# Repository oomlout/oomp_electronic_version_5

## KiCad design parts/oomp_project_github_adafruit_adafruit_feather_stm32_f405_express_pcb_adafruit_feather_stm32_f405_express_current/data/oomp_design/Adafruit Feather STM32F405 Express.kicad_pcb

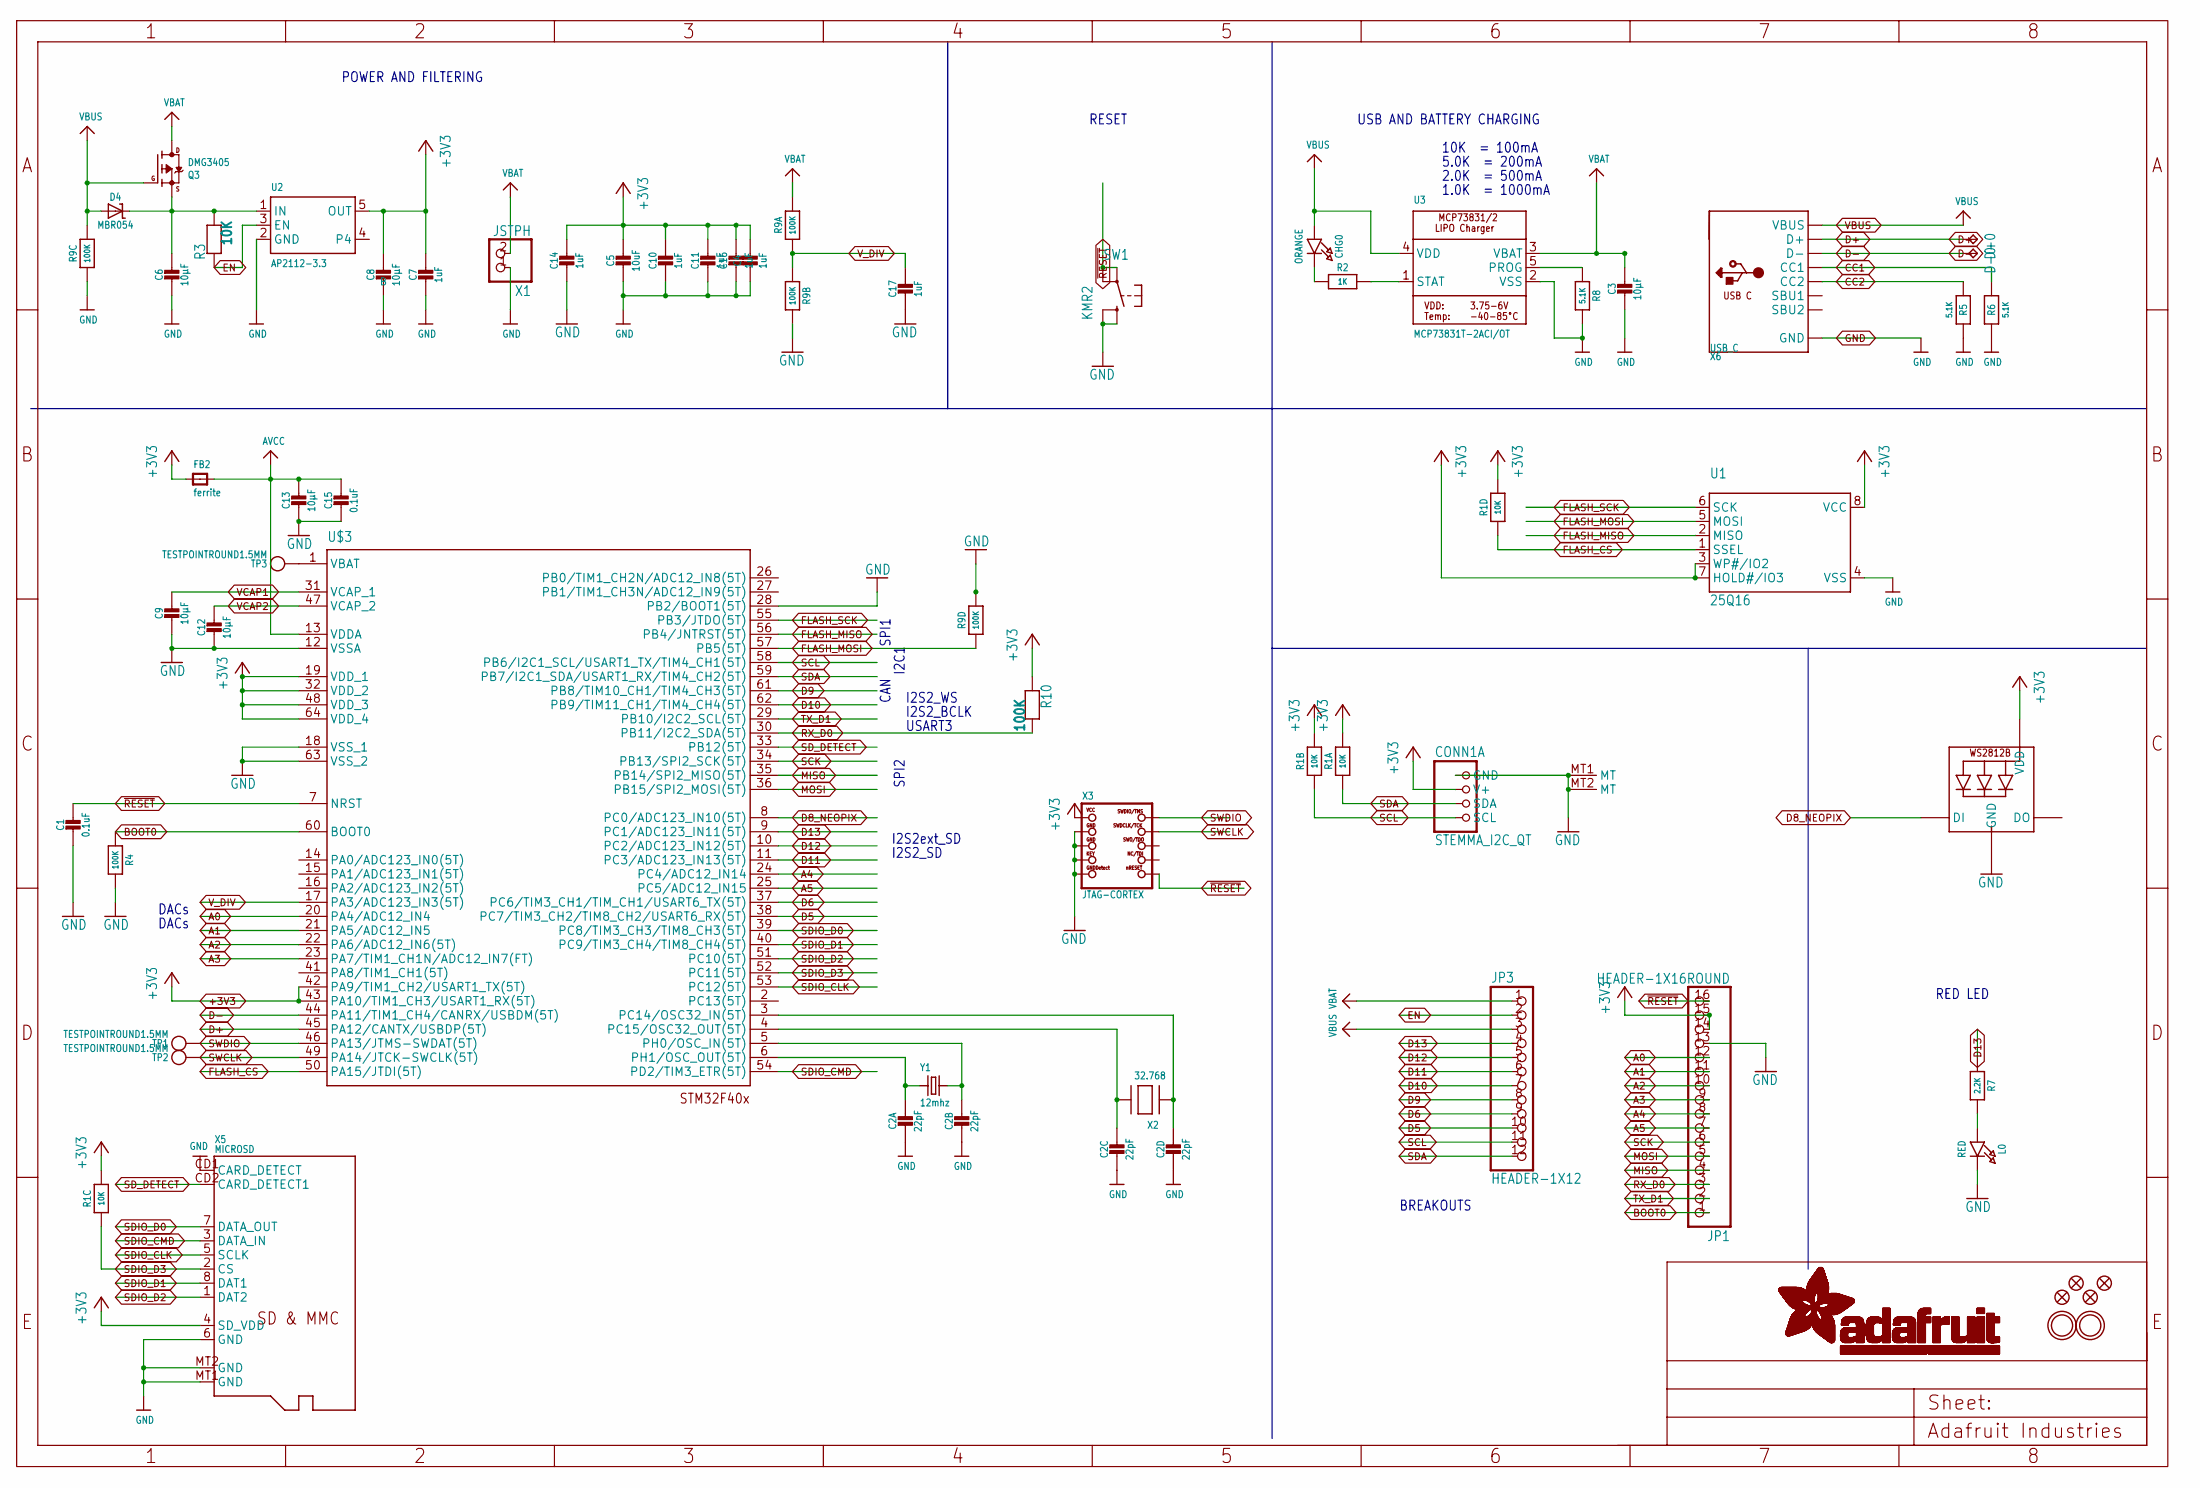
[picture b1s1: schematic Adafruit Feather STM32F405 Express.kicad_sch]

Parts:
C1, C15: 0.1uF; 0603-NO
C2: 22pF; RESPACK_4X0603
C3, C6, C8, C9, C12, C13: 10µF; 0805-NO
C4, C7, C10, C11, C14, C16, C17: 1uF; 0603-NO
C5: 10uF; 0805-NO
CHG0: ORANGE; CHIPLED_0805_NOOUTLINE
CONN1: STEMMA_I2C_QT; JST_SH4
D4: MBR054; SOD-123
D+0: TPB1,27; B1,27
D-0: TPB1,27; B1,27
FB2: ferrite; 0805-NO
JP1: HEADER-1X16ROUND; 1X16_ROUND
JP3: HEADER-1X12; 1X12_ROUND
L0: RED; CHIPLED_0805_NOOUTLINE
LED1: WS2812B3535; LED3535
Q3: DMG3405; SOT23-R
R1: 10K; RESPACK_4X0603_NO
R2: 1K; 0603-NO
R3: 10K; 0603-NO
R4, R10: 100K; 0603-NO
R5, R6, R8: 5.1K; 0603-NO
R7: 2.2K; 0603-NO
R9: 100K; RESPACK_4X0603_NO
SW1: KMR2; BTN_KMR2_4.6X2.8
TP1, TP2, TP3: TESTPOINTROUND1.5MM; TESTPOINT_ROUND_1.5MM
U1: 25Q16; SOIC8_150MIL
U2: AP2112-3.3; SOT23-5
U3: MCP73831T-2ACI/OT; SOT23-5
U$3: STM32F405R; TQFP64
U$5, U$34, U$35, U$37: FIDUCIAL_1MM
U$31, U$32: MOUNTINGHOLE2.5; MOUNTINGHOLE_2.5_PLATED
X1: JSTPH; JSTPH2
X2: 32.768; XTAL3215
X3: JTAG-CORTEX; 2X05_1.27MM_SMT
X5: MICROSD
X6: USB_C; USB_C_CUSB31-CFM2AX-01-X
Y1: 12mhz; CRYSTAL_2.5X2

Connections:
+3V3: C4.1, C5.1, C7.1, C8.1, C10.1, C11.1, C14.1, C16.1, CONN1.2 (V+), FB2.1, JP1.14, JP1.15, LED1.2 (VDD), R1.5 (2), R1.6 (2), R1.7 (2), R1.8 (2), R10.1, U1.3 (WP#/IO2), U1.7 (HOLD#/IO3), U1.8 (VCC), U2.5 (OUT), U$3.19 (VDD_1), U$3.32 (VDD_2), U$3.42 (PA9/TIM1_CH2/USART1_TX(5T)), U$3.43 (PA10/TIM1_CH3/USART1_RX(5T)), U$3.48 (VDD_3), U$3.64 (VDD_4), X3.1 (VCC), X5.4 (SD_VDD)
A0: JP1.12, U$3.20 (PA4/ADC12_IN4)
A1: JP1.11, U$3.21 (PA5/ADC12_IN5)
A2: JP1.10, U$3.22 (PA6/ADC12_IN6(5T))
A3: JP1.9, U$3.23 (PA7/TIM1_CH1N/ADC12_IN7(FT))
A4: JP1.8, U$3.24 (PC4/ADC12_IN14)
A5: JP1.7, U$3.25 (PC5/ADC12_IN15)
AVCC: C13.1, C15.1, FB2.2, U$3.13 (VDDA)
BATTERY: TP3.P$1, U$3.1 (VBAT)
BOOT0: JP1.1, R4.1, U$3.60 (BOOT0)
CC1: R6.2, X6.A5 (CC1)
CC2: R5.2, X6.B5 (CC2)
D5: JP3.10, U$3.38 (PC7/TIM3_CH2/TIM8_CH2/USART6_RX(5T))
D6: JP3.9, U$3.37 (PC6/TIM3_CH1/TIM_CH1/USART6_TX(5T))
D8_NEOPIX: LED1.1 (DI), U$3.8 (PC0/ADC123_IN10(5T))
D9: JP3.8, U$3.61 (PB8/TIM10_CH1/TIM4_CH3(5T))
D10: JP3.7, U$3.62 (PB9/TIM11_CH1/TIM4_CH4(5T))
D11: JP3.6, U$3.11 (PC3/ADC123_IN13(5T))
D12: JP3.5, U$3.10 (PC2/ADC123_IN12(5T))
D13: JP3.4, R7.1, U$3.9 (PC1/ADC123_IN11(5T))
D+: D+0.TP, U$3.45 (PA12/CANTX/USBDP(5T)), X6.A6 (D+), X6.B6 (D+)
D-: D-0.TP, U$3.44 (PA11/TIM1_CH4/CANRX/USBDM(5T)), X6.A7 (D-), X6.B7 (D-)
EN: JP3.2, R3.1, U2.3 (EN)
FLASH_CS: R1.4 (1), U1.1 (SSEL), U$3.50 (PA15/JTDI(5T))
FLASH_MISO: U1.2 (MISO), U$3.56 (PB4/JNTRST(5T))
FLASH_MOSI: R9.4 (1), U1.5 (MOSI), U$3.57 (PB5(5T))
FLASH_SCK: U1.6 (SCK), U$3.55 (PB3/JTDO(5T))
GND: C1.2, C2.5 (2), C2.6 (2), C2.7 (2), C2.8 (2), C3.2, C4.2, C5.2, C6.2, C7.2, C8.2, C9.2, C10.2, C11.2, C12.2, C13.2, C14.2, C15.2, C16.2, C17.2, CONN1.1 (GND), CONN1.MT1 (MT), CONN1.MT2 (MT), JP1.13, L0.C, LED1.4 (GND), R4.2, R5.1, R6.1, R8.2, R9.3 (1), R9.5 (2), R9.7 (2), SW1.B (S), SW1.B' (S1), U1.4 (VSS), U2.2 (GND), U3.2 (VSS), U$3.12 (VSSA), U$3.18 (VSS_1), U$3.28 (PB2/BOOT1(5T)), U$3.63 (VSS_2), X1.1, X3.3 (GND), X3.5 (GND), X3.7 (KEY), X3.9 (GNDDETECT), X5.6 (GND), X5.CD1 (CARD_DETECT), X5.MT1 (GND), X5.MT2 (GND), X6.A1B12 (GND), X6.B1A12 (GND)
MISO: JP1.4, U$3.35 (PB14/SPI2_MISO(5T))
MOSI: JP1.5, U$3.36 (PB15/SPI2_MOSI(5T))
unnamed: CHG0.C, R2.1
unnamed: L0.A, R7.2
unnamed: R2.2, U3.1 (STAT)
unnamed: R8.1, U3.5 (PROG)
unnamed: C2.4 (1), U$3.3 (PC14/OSC32_IN(5T)), X2.P$1
unnamed: C2.2 (1), U$3.5 (PH0/OSC_IN(5T)), Y1.3 (2)
unnamed: C2.3 (1), U$3.4 (PC15/OSC32_OUT(5T)), X2.P$2
unnamed: C2.1, U$3.6 (PH1/OSC_OUT(5T)), Y1.1
RX_D0: JP1.3, R10.2, U$3.30 (PB11/I2C2_SDA(5T))
SCK: JP1.6, U$3.34 (PB13/SPI2_SCK(5T))
SCL: CONN1.4 (SCL), JP3.11, R1.2 (1), U$3.58 (PB6/I2C1_SCL/USART1_TX/TIM4_CH1(5T))
SDA: CONN1.3 (SDA), JP3.12, R1.1, U$3.59 (PB7/I2C1_SDA/USART1_RX/TIM4_CH2(5T))
SDIO_CLK: U$3.53 (PC12(5T)), X5.5 (SCLK)
SDIO_CMD: U$3.54 (PD2/TIM3_ETR(5T)), X5.3 (DATA_IN)
SDIO_D0: U$3.39 (PC8/TIM3_CH3/TIM8_CH3(5T)), X5.7 (DATA_OUT)
SDIO_D1: U$3.40 (PC9/TIM3_CH4/TIM8_CH4(5T)), X5.8 (DAT1)
SDIO_D2: U$3.51 (PC10(5T)), X5.1 (DAT2)
SDIO_D3: R1.3 (1), U$3.52 (PC11(5T)), X5.2 (CS)
SD_DETECT: U$3.33 (PB12(5T)), X5.CD2 (CARD_DETECT1)
SWCLK: TP2.P$1, U$3.49 (PA14/JTCK-SWCLK(5T)), X3.4 (SWDCLK)
SWDIO: TP1.P$1, U$3.46 (PA13/JTMS-SWDAT(5T)), X3.2 (SWDIO)
TX_D1: JP1.2, U$3.29 (PB10/I2C2_SCL(5T))
VBAT: C3.1, JP3.1, Q3.3 (D), R9.8 (2), U3.3 (VBAT), X1.2
VBUS: CHG0.A, D4.A, JP3.3, Q3.1 (G), R9.6 (2), U3.4 (VDD), X6.A4B9 (VBUS), X6.B4A9 (VBUS)
VCAP1: C9.1, U$3.31 (VCAP_1)
VCAP2: C12.1, U$3.47 (VCAP_2)
VHI: C6.1, D4.C, Q3.2 (S), R3.2, U2.1 (IN)
V_DIV: C17.1, R9.1, R9.2 (1), U$3.17 (PA3/ADC123_IN3(5T))
~RESET: C1.1, JP1.16, SW1.A, SW1.A' (P1), U$3.7 (NRST), X3.10 (NRESET)

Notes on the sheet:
USART3
1.0K = 1000mA
5.0K = 200mA
USB AND BATTERY CHARGING
RED LED
I2S2_SD
10K = 100mA
DACs
SPI2
SPI1
I2S2_BCLK
2.0K = 500mA
I2C1
POWER AND FILTERING
I2S2_WS
RESET
I2S2ext_SD
CAN
BREAKOUTS

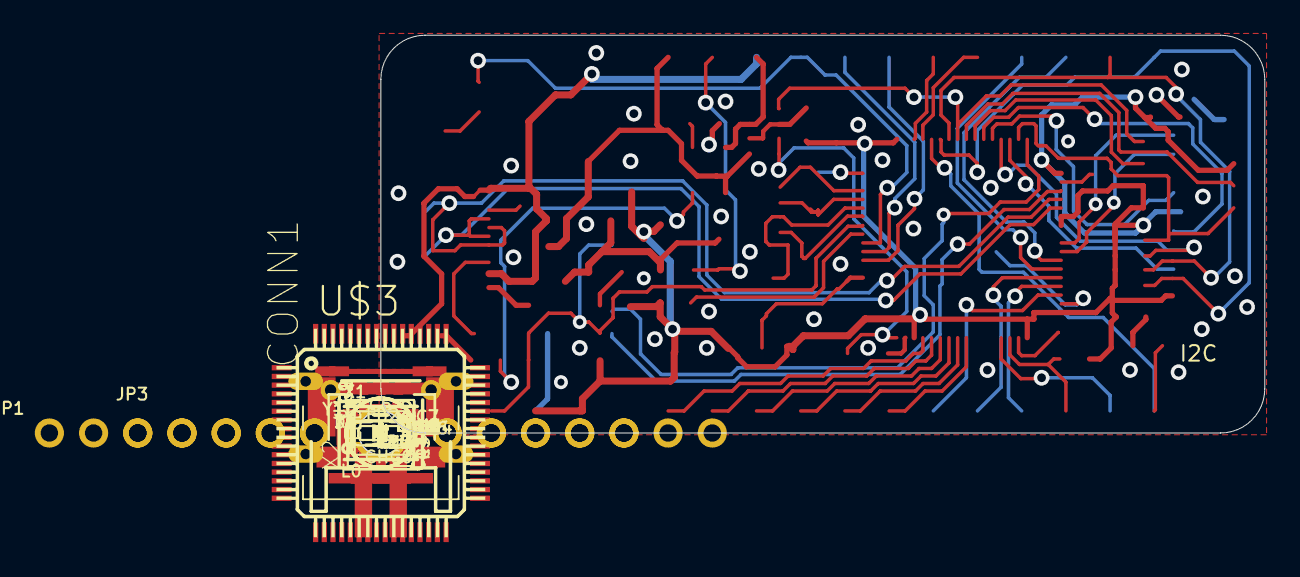
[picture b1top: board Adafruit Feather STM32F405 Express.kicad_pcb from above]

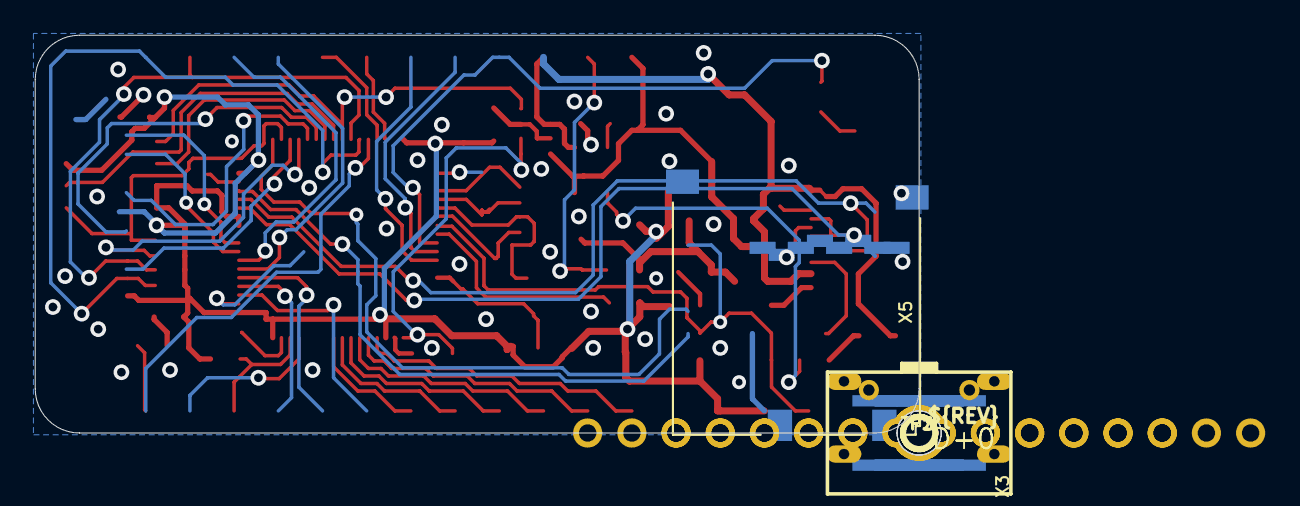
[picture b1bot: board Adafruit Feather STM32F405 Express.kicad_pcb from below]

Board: 2 copper layers, 50.8 x 22.9 mm, 63 parts (11 on the bottom side), 59 nets.

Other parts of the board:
U$13: PCBFEAT-REV-040
U$24: FEATHER_STM32F405_TOP
U$40: FEATHER_STM32F405_BOT
UNK_HOLE_0: dummyfp0
UNK_HOLE_1: dummyfp1

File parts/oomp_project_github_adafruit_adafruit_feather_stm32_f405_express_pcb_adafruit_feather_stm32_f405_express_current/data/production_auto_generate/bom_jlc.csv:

Comment,Designator,Footprint,LCSC Part #
,JP3,Adafruit Feather STM32F405 Express-import-fps:1X12_ROUND,C7501588
,JP1,Adafruit Feather STM32F405 Express-import-fps:1X16_ROUND,C7501270
,X3,Adafruit Feather STM32F405 Express-import-fps:2X05_1.27MM_SMT,
,U$40,Adafruit Feather STM32F405 Express-import-fps:FEATHER_STM32F405_BOT,
,U$24,Adafruit Feather STM32F405 Express-import-fps:FEATHER_STM32F405_TOP,
,X5,Adafruit Feather STM32F405 Express-import-fps:MICROSD,
,U$13,Adafruit Feather STM32F405 Express-import-fps:PCBFEAT-REV-040,
,"TP1,TP2,TP3",Adafruit Feather STM32F405 Express-import-fps:TESTPOINT_ROUND_1.5MM,
,X6,Adafruit Feather STM32F405 Express-import-fps:USB_C_CUSB31-CFM2AX-01-X,
0.1uF,"C1,C15",Adafruit Feather STM32F405 Express-import-fps:0603-NO,C14663
100K,"R4,R10",Adafruit Feather STM32F405 Express-import-fps:0603-NO,C25803
100K,R9,Adafruit Feather STM32F405 Express-import-fps:RESPACK_4X0603_NO,C25803
10K,R3,Adafruit Feather STM32F405 Express-import-fps:0603-NO,C98220
10K,R1,Adafruit Feather STM32F405 Express-import-fps:RESPACK_4X0603_NO,C98220
10uF,C5,Adafruit Feather STM32F405 Express-import-fps:0805-NO,
10µF,"C3,C6,C8,C9,C12,C13",Adafruit Feather STM32F405 Express-import-fps:0805-NO,
12mhz,Y1,Adafruit Feather STM32F405 Express-import-fps:CRYSTAL_2.5X2,
1K,R2,Adafruit Feather STM32F405 Express-import-fps:0603-NO,C2907002
1uF,"C4,C7,C10,C11,C14,C16,C17",Adafruit Feather STM32F405 Express-import-fps:0603-NO,C5673
2.2K,R7,Adafruit Feather STM32F405 Express-import-fps:0603-NO,C4190
22pF,C2,Adafruit Feather STM32F405 Express-import-fps:RESPACK_4X0603,C105620
25Q16,U1,Adafruit Feather STM32F405 Express-import-fps:SOIC8_150MIL,
32.768,X2,Adafruit Feather STM32F405 Express-import-fps:XTAL3215,
5.1K,"R5,R6,R8",Adafruit Feather STM32F405 Express-import-fps:0603-NO,C23186
AP2112-3.3,U2,Adafruit Feather STM32F405 Express-import-fps:SOT23-5,
DMG3405,Q3,Adafruit Feather STM32F405 Express-import-fps:SOT23-R,
ferrite,FB2,Adafruit Feather STM32F405 Express-import-fps:0805-NO,
FIDUCIAL_1MM,"U$5,U$34,U$35,U$37",Adafruit Feather STM32F405 Express-import-fps:FIDUCIAL_1MM,
JSTPH,X1,Adafruit Feather STM32F405 Express-import-fps:JSTPH2,
KMR2,SW1,Adafruit Feather STM32F405 Express-import-fps:BTN_KMR2_4.6X2.8,
MBR054,D4,Adafruit Feather STM32F405 Express-import-fps:SOD-123,
MCP73831T-2ACI/OT,U3,Adafruit Feather STM32F405 Express-import-fps:SOT23-5,
ORANGE,CHG0,Adafruit Feather STM32F405 Express-import-fps:CHIPLED_0805_NOOUTLINE,
RED,L0,Adafruit Feather STM32F405 Express-import-fps:CHIPLED_0805_NOOUTLINE,
STEMMA_I2C_QT,CONN1,Adafruit Feather STM32F405 Express-import-fps:JST_SH4,C160404
STM32F405R,U$3,Adafruit Feather STM32F405 Express-import-fps:TQFP64,
"TPB1,27","D+0,D-0","Adafruit Feather STM32F405 Express-import-fps:B1,27",
WS2812B3535,LED1,Adafruit Feather STM32F405 Express-import-fps:LED3535,

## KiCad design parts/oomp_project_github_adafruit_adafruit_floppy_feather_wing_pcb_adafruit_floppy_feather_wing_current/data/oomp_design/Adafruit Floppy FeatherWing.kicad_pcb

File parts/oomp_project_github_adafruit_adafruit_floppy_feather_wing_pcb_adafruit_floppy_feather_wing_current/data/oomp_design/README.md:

# OOMP KiCad design copy

Open `Adafruit Floppy FeatherWing.kicad_pro` (or the `.kicad_pcb` / `.kicad_sch`) in KiCad. Local OOMP libraries are under `libraries/`. Original inputs are preserved in [../original/](../original/).

Only verified unchanged installed KiCad defaults were renamed. Modified, custom, unmatched and unavailable items remain unchanged. Soldering variants are never swapped during conversion. Existing pad coordinates, nets and UUIDs are preserved.

See [conversion_report.yaml](conversion_report.yaml) for every conversion and skip. Copy this directory before editing; regeneration refuses to overwrite edited design files.

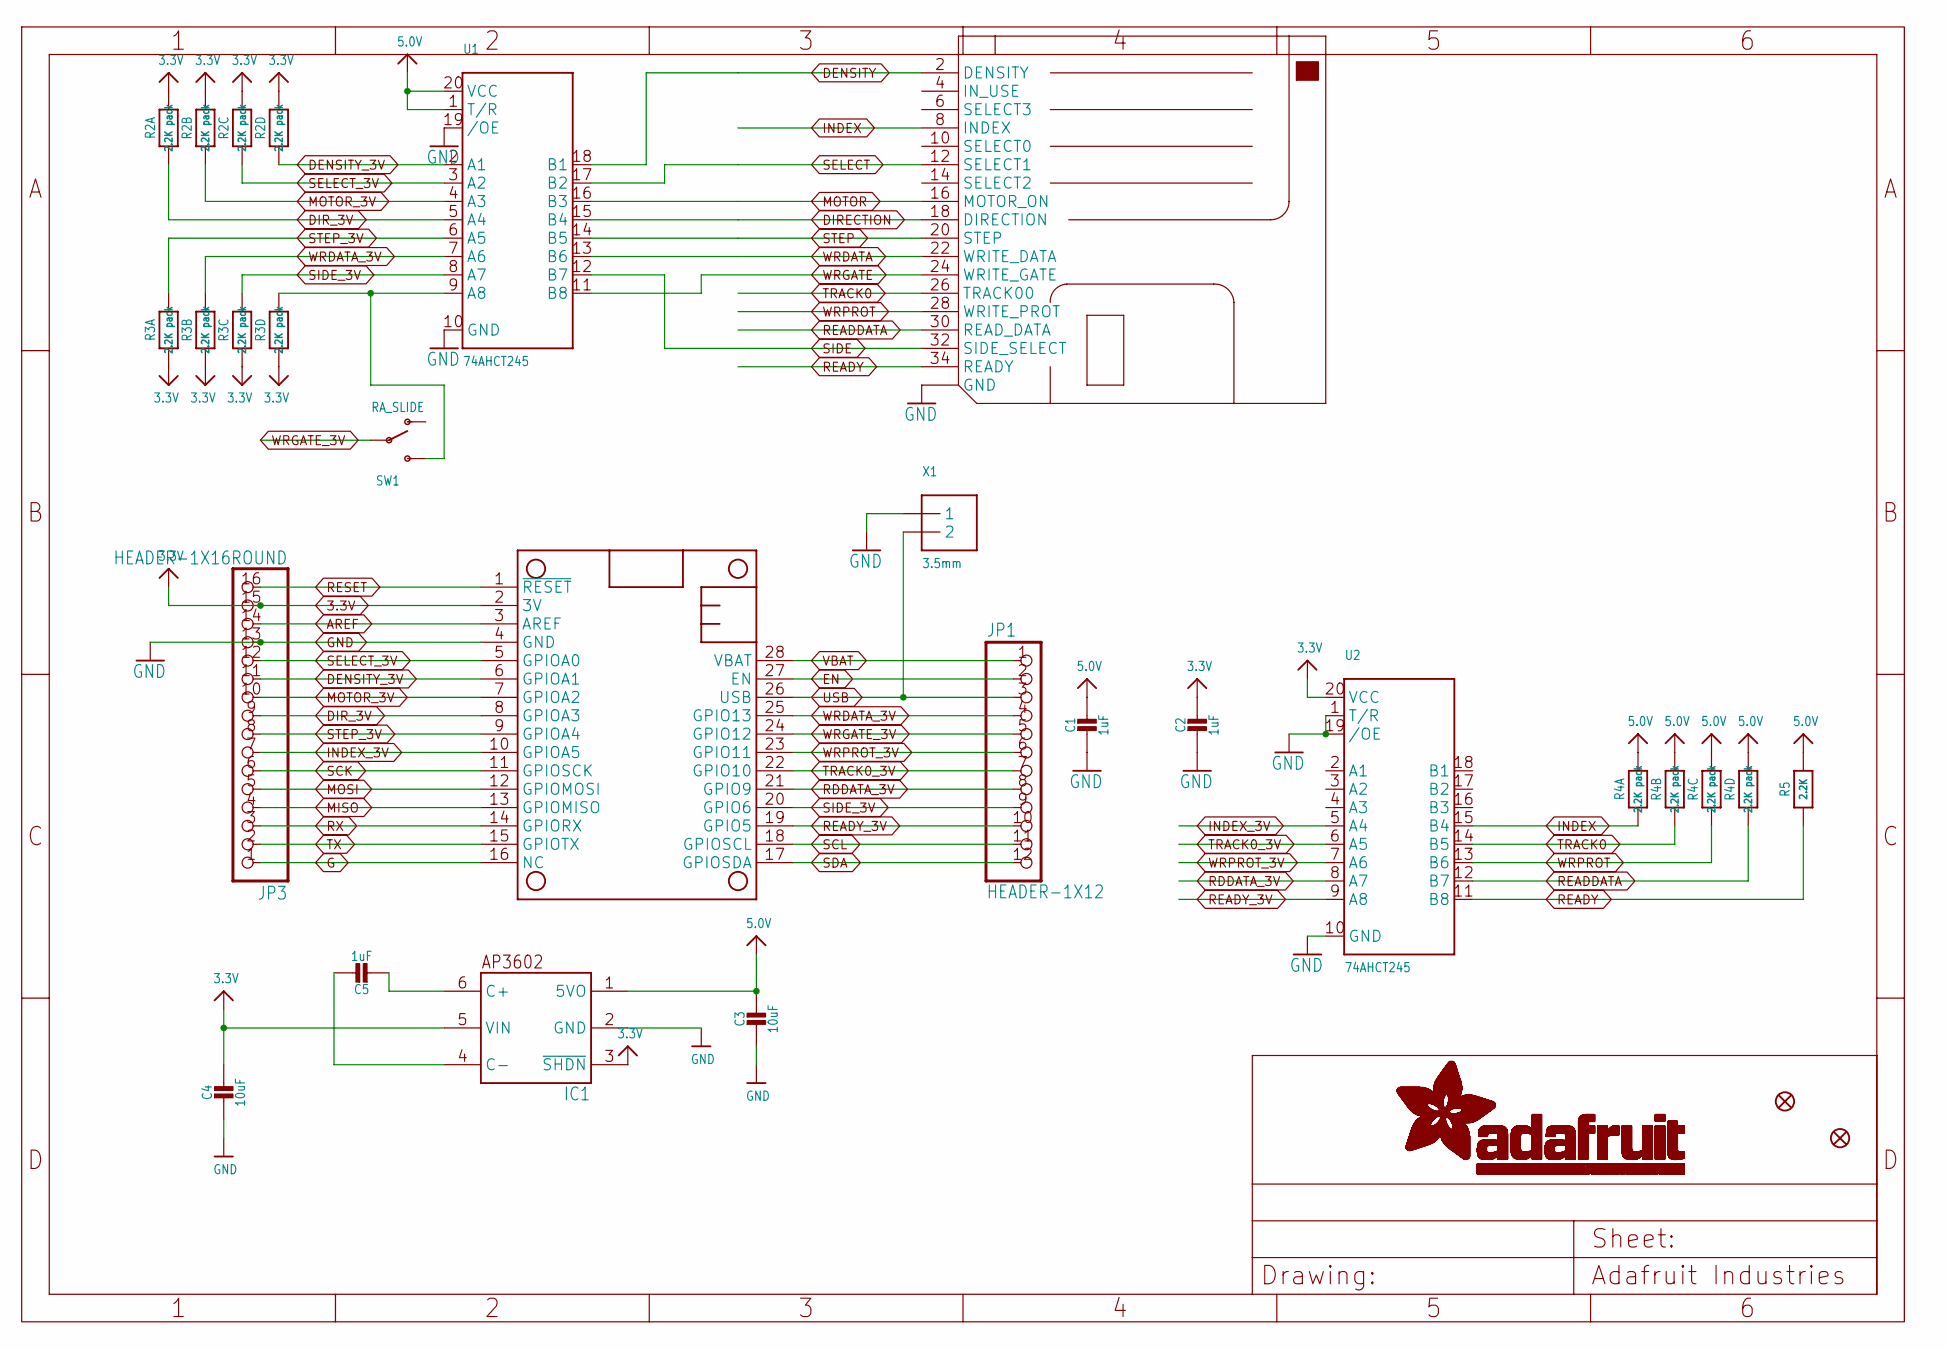
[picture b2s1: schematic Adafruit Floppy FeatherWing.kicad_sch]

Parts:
C1, C2, C5: 1uF; 0603-NO
C3, C4: 10uF; 0805-NO
FDD1: FLOPPY_IDC_SMT; 2X17_FLOPPY_SMTIDC
FID1, FID2: FIDUCIAL_1MM
IC1: AP3602; SOT23-6
JP1: HEADER-1X12; 1X12_ROUND
JP3: HEADER-1X16ROUND; 1X16_ROUND
MS1: FEATHERWING
R2, R3, R4: 2.2K pack; RESPACK_4X0603
R5: 2.2K; 0603-NO
SW1: RA_SLIDE; SPDT_SMT_SSSS811101
U1, U2: 74AHCT245; SSOP20
X1: 3.5mm; TERMBLOCK_1X2-3.5MM

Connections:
3.3V: C2.1, C4.1, IC1.3 (~SHDN), IC1.5 (VIN), JP3.15, MS1.2 (3V), R2.5 (2), R2.6 (2), R2.7 (2), R2.8 (2), R3.1, R3.2 (1), R3.3 (1), R3.4 (1), U2.20 (VCC)
5.0V: C1.1, C3.1, IC1.1 (5VO), R4.5 (2), R4.6 (2), R4.7 (2), R4.8 (2), R5.2, U1.1 (T/R), U1.20 (VCC)
AREF: JP3.14, MS1.3 (AREF)
DENSITY: FDD1.2 (DENSITY), U1.18 (B1)
DENSITY_3V: JP3.11, MS1.6 (GPIOA1), R2.4 (1), U1.2 (A1)
DIRECTION: FDD1.18 (DIRECTION), U1.15 (B4)
DIR_3V: JP3.9, MS1.8 (GPIOA3), R2.1, U1.5 (A4)
EN: JP1.2, MS1.27 (EN)
G: JP3.1, MS1.16 (NC)
GND: C1.2, C2.2, C3.2, C4.2, FDD1.1 (GND), FDD1.3 (GND), FDD1.5 (GND), FDD1.7 (GND), FDD1.9 (GND), FDD1.11 (GND), FDD1.13 (GND), FDD1.15 (GND), FDD1.17 (GND), FDD1.19 (GND), FDD1.21 (GND), FDD1.23 (GND), FDD1.25 (GND), FDD1.27 (GND), FDD1.29 (GND), FDD1.31 (GND), FDD1.33 (GND), IC1.2 (GND), JP3.13, MS1.4 (GND), U1.10 (GND), U1.19 (/OE), U2.1 (T/R), U2.10 (GND), U2.19 (/OE), X1.1
INDEX: FDD1.8 (INDEX), R4.1, U2.15 (B4)
INDEX_3V: JP3.7, MS1.10 (GPIOA5), U2.5 (A4)
MISO: JP3.4, MS1.13 (GPIOMISO)
MOSI: JP3.5, MS1.12 (GPIOMOSI)
MOTOR: FDD1.16 (MOTOR_ON), U1.16 (B3)
MOTOR_3V: JP3.10, MS1.7 (GPIOA2), R2.2 (1), U1.4 (A3)
unnamed: R3.5 (2), SW1.C (S), U1.9 (A8)
unnamed: C5.2, IC1.6 (C+)
unnamed: C5.1, IC1.4 (C-)
RDDATA_3V: JP1.8, MS1.21 (GPIO9), U2.8 (A7)
READDATA: FDD1.30 (READ_DATA), R4.4 (1), U2.12 (B7)
READY: FDD1.34 (READY), R5.1, U2.11 (B8)
READY_3V: JP1.10, MS1.19 (GPIO5), U2.9 (A8)
RESET: JP3.16, MS1.1 (~RESET)
RX: JP3.3, MS1.14 (GPIORX)
SCK: JP3.6, MS1.11 (GPIOSCK)
SCL: JP1.11, MS1.18 (GPIOSCL)
SDA: JP1.12, MS1.17 (GPIOSDA)
SELECT: FDD1.12 (SELECT1), U1.17 (B2)
SELECT_3V: JP3.12, MS1.5 (GPIOA0), R2.3 (1), U1.3 (A2)
SIDE: FDD1.32 (SIDE_SELECT), U1.12 (B7)
SIDE_3V: JP1.9, MS1.20 (GPIO6), R3.6 (2), U1.8 (A7)
STEP: FDD1.20 (STEP), U1.14 (B5)
STEP_3V: JP3.8, MS1.9 (GPIOA4), R3.8 (2), U1.6 (A5)
TRACK0: FDD1.26 (TRACK00), R4.2 (1), U2.14 (B5)
TRACK0_3V: JP1.7, MS1.22 (GPIO10), U2.6 (A5)
TX: JP3.2, MS1.15 (GPIOTX)
USB: JP1.3, MS1.26 (USB), X1.2
VBAT: JP1.1, MS1.28 (VBAT)
WRDATA: FDD1.22 (WRITE_DATA), U1.13 (B6)
WRDATA_3V: JP1.4, MS1.25 (GPIO13), R3.7 (2), U1.7 (A6)
WRGATE: FDD1.24 (WRITE_GATE), U1.11 (B8)
WRGATE_3V: JP1.5, MS1.24 (GPIO12), SW1.B
WRPROT: FDD1.28 (WRITE_PROT), R4.3 (1), U2.13 (B6)
WRPROT_3V: JP1.6, MS1.23 (GPIO11), U2.7 (A6)

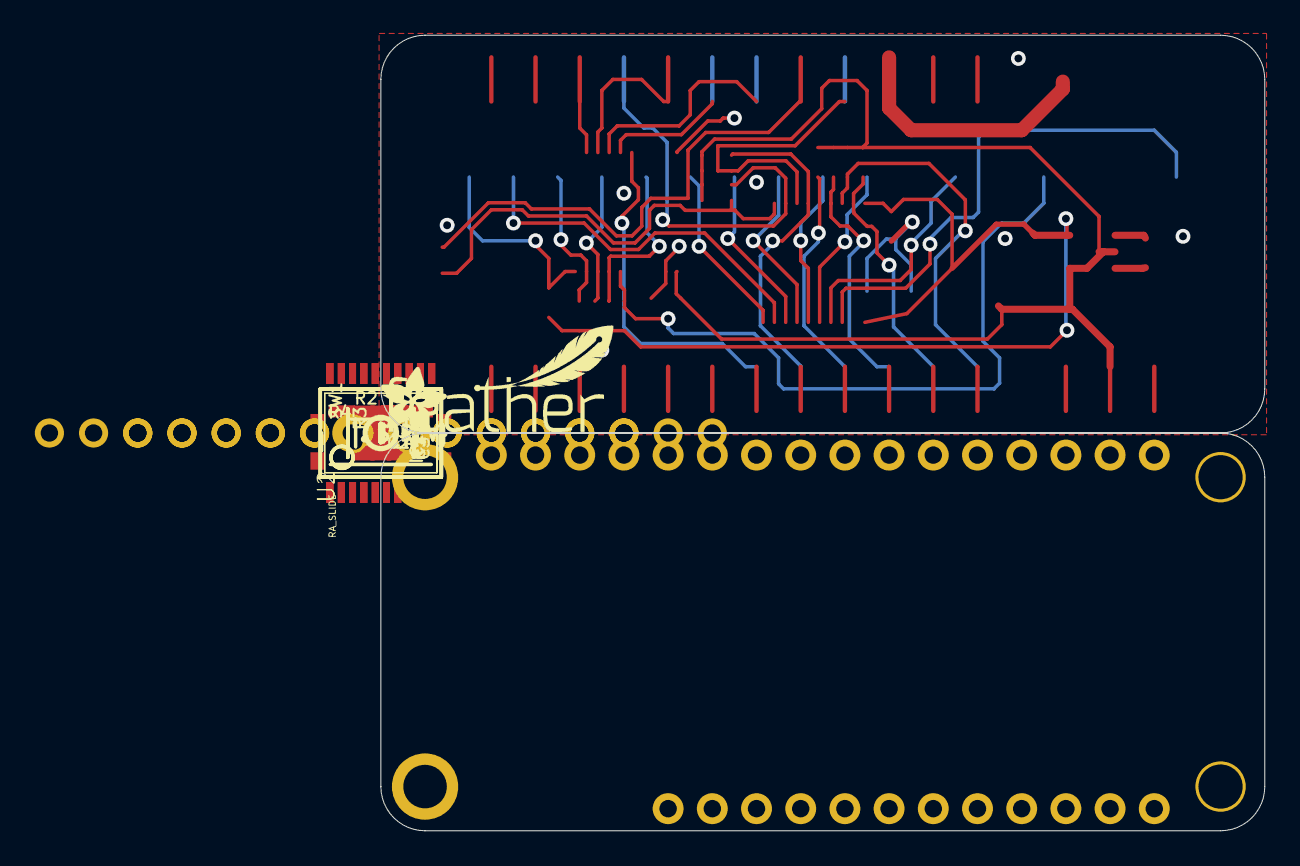
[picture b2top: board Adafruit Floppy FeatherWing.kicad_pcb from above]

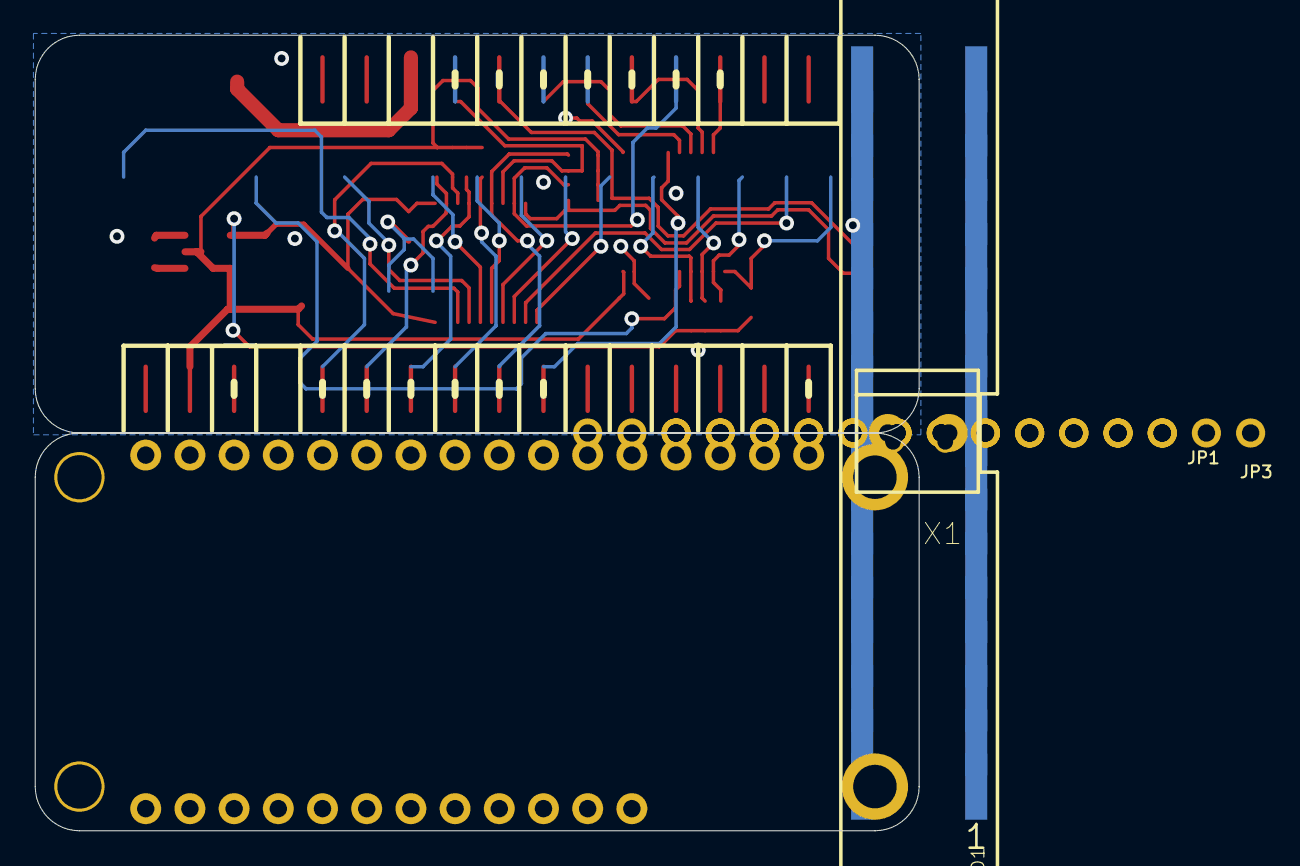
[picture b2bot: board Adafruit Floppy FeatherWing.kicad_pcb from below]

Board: 2 copper layers, 50.8 x 45.7 mm, 59 parts (26 on the bottom side), 45 nets.

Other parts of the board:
PLABEL0: PLABEL0
PLABEL1: PLABEL1
PLABEL2: PLABEL2
PLABEL3: PLABEL3
PLABEL4: PLABEL4
PLABEL5: PLABEL5
PLABEL6: PLABEL6
PLABEL7: PLABEL7
PLABEL8: PLABEL8
PLABEL9: PLABEL9
PLABEL10: PLABEL10
PLABEL11: PLABEL11
PLABEL12: PLABEL12
PLABEL13: PLABEL13
PLABEL14: PLABEL14
PLABEL15: PLABEL15
PLABEL16: PLABEL16
PLABEL17: PLABEL17
PLABEL18: PLABEL18
PLABEL19: PLABEL19
PLABEL20: PLABEL20
PLABEL21: PLABEL21
PLABEL22: PLABEL22
PLABEL23: PLABEL23
PLABEL24: PLABEL24
PLABEL25: PLABEL25
PLABEL26: PLABEL26
PLABEL27: PLABEL27
PLABEL28: PLABEL28
PLABEL29: PLABEL29
PLABEL30: PLABEL30
PLABEL31: PLABEL31
PLABEL32: PLABEL32
PLABEL33: PLABEL33
PLABEL34: PLABEL34
PLABEL35: PLABEL35
U$26: PCBFEAT-REV-040
U$27: FEATHERLOGO_SMALL
U$28: ADAFRUIT_3.5MM

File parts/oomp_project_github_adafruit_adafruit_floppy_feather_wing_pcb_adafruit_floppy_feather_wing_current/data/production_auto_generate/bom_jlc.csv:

Comment,Designator,Footprint,LCSC Part #
,JP1,Adafruit Floppy FeatherWing-import-fps:1X12_ROUND,C7501588
,JP3,Adafruit Floppy FeatherWing-import-fps:1X16_ROUND,C7501270
,U$28,Adafruit Floppy FeatherWing-import-fps:ADAFRUIT_3.5MM,
,U$27,Adafruit Floppy FeatherWing-import-fps:FEATHERLOGO_SMALL,
,U$26,Adafruit Floppy FeatherWing-import-fps:PCBFEAT-REV-040,
,PLABEL0,Adafruit Floppy FeatherWing-import-fps:PLABEL0,
,PLABEL1,Adafruit Floppy FeatherWing-import-fps:PLABEL1,
,PLABEL10,Adafruit Floppy FeatherWing-import-fps:PLABEL10,
,PLABEL11,Adafruit Floppy FeatherWing-import-fps:PLABEL11,
,PLABEL12,Adafruit Floppy FeatherWing-import-fps:PLABEL12,
,PLABEL13,Adafruit Floppy FeatherWing-import-fps:PLABEL13,
,PLABEL14,Adafruit Floppy FeatherWing-import-fps:PLABEL14,
,PLABEL15,Adafruit Floppy FeatherWing-import-fps:PLABEL15,
,PLABEL16,Adafruit Floppy FeatherWing-import-fps:PLABEL16,
,PLABEL17,Adafruit Floppy FeatherWing-import-fps:PLABEL17,
,PLABEL18,Adafruit Floppy FeatherWing-import-fps:PLABEL18,
,PLABEL19,Adafruit Floppy FeatherWing-import-fps:PLABEL19,
,PLABEL2,Adafruit Floppy FeatherWing-import-fps:PLABEL2,
,PLABEL20,Adafruit Floppy FeatherWing-import-fps:PLABEL20,
,PLABEL21,Adafruit Floppy FeatherWing-import-fps:PLABEL21,
,PLABEL22,Adafruit Floppy FeatherWing-import-fps:PLABEL22,
,PLABEL23,Adafruit Floppy FeatherWing-import-fps:PLABEL23,
,PLABEL24,Adafruit Floppy FeatherWing-import-fps:PLABEL24,
,PLABEL25,Adafruit Floppy FeatherWing-import-fps:PLABEL25,
,PLABEL26,Adafruit Floppy FeatherWing-import-fps:PLABEL26,
,PLABEL27,Adafruit Floppy FeatherWing-import-fps:PLABEL27,
,PLABEL28,Adafruit Floppy FeatherWing-import-fps:PLABEL28,
,PLABEL29,Adafruit Floppy FeatherWing-import-fps:PLABEL29,
,PLABEL3,Adafruit Floppy FeatherWing-import-fps:PLABEL3,
,PLABEL30,Adafruit Floppy FeatherWing-import-fps:PLABEL30,
,PLABEL31,Adafruit Floppy FeatherWing-import-fps:PLABEL31,
,PLABEL32,Adafruit Floppy FeatherWing-import-fps:PLABEL32,
,PLABEL33,Adafruit Floppy FeatherWing-import-fps:PLABEL33,
,PLABEL34,Adafruit Floppy FeatherWing-import-fps:PLABEL34,
,PLABEL35,Adafruit Floppy FeatherWing-import-fps:PLABEL35,
,PLABEL4,Adafruit Floppy FeatherWing-import-fps:PLABEL4,
,PLABEL5,Adafruit Floppy FeatherWing-import-fps:PLABEL5,
,PLABEL6,Adafruit Floppy FeatherWing-import-fps:PLABEL6,
,PLABEL7,Adafruit Floppy FeatherWing-import-fps:PLABEL7,
,PLABEL8,Adafruit Floppy FeatherWing-import-fps:PLABEL8,
,PLABEL9,Adafruit Floppy FeatherWing-import-fps:PLABEL9,
10uF,"C3,C4",Adafruit Floppy FeatherWing-import-fps:0805-NO,
1uF,"C1,C2,C5",Adafruit Floppy FeatherWing-import-fps:0603-NO,C5673
2.2K,R5,Adafruit Floppy FeatherWing-import-fps:0603-NO,C4190
2.2K pack,"R2,R3,R4",Adafruit Floppy FeatherWing-import-fps:RESPACK_4X0603,C4190
3.5mm,X1,Adafruit Floppy FeatherWing-import-fps:TERMBLOCK_1X2-3.5MM,
74AHCT245,"U1,U2",Adafruit Floppy FeatherWing-import-fps:SSOP20,
AP3602,IC1,Adafruit Floppy FeatherWing-import-fps:SOT23-6,
FEATHERWING,MS1,Adafruit Floppy FeatherWing-import-fps:FEATHERWING,
FLOPPY_IDC_SMT,FDD1,Adafruit Floppy FeatherWing-import-fps:2X17_FLOPPY_SMTIDC,
RA_SLIDE,SW1,Adafruit Floppy FeatherWing-import-fps:SPDT_SMT_SSSS811101,
